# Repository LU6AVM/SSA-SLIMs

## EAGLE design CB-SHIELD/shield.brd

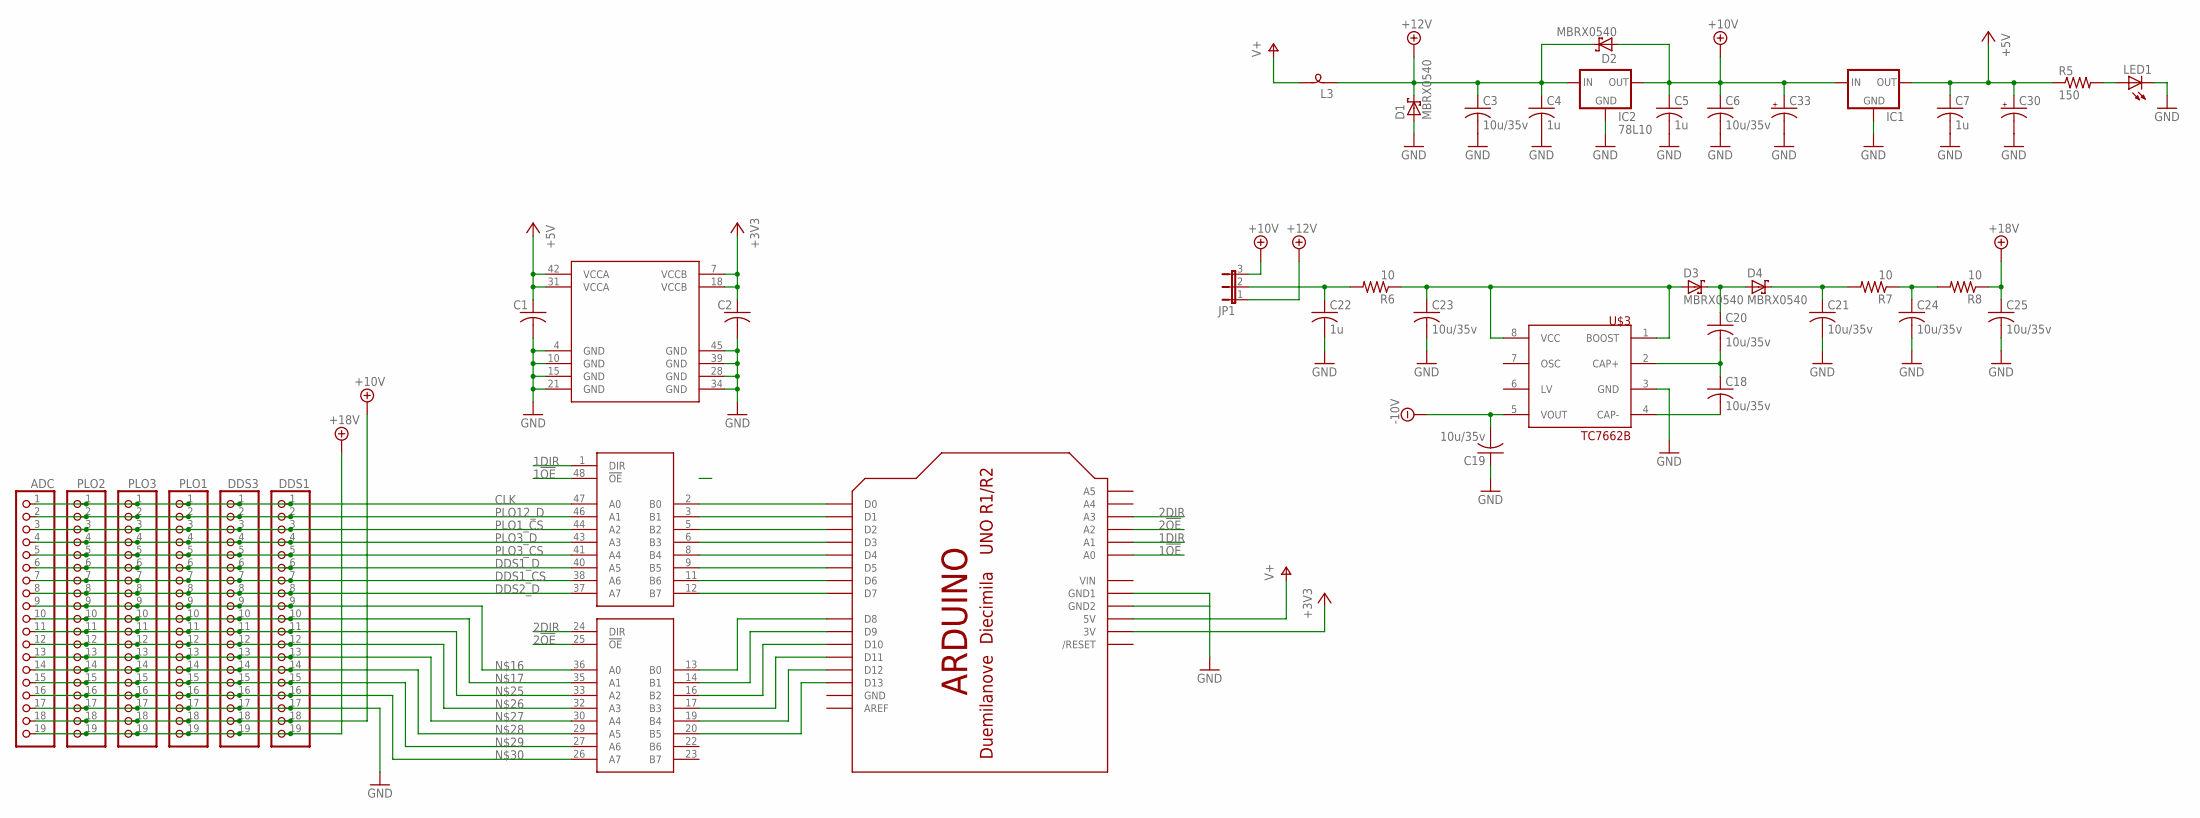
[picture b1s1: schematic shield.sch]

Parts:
ADC: PINHD-1X19; 1X19
C1, C2: C-USC0805; C0805
C3, C6, C18, C19, C20, C21, C23, C24, C25: 10u/35v; C1206
C4, C5, C7, C22: 1u; C0603
C30, C33: CPOL-USE2.5-6; E2,5-6
D1, D2, D3, D4: MBRX0540; SOD323-R
DDS1, DDS3: PINHD-1X19; 1X19
IC1: 78MXXLSOT-89; SOT89-BCE
IC2: 78L10; 78XXS
JP1: JP2E; JP2
L3: SM-B5
LED1: LED5MM
PLO1, PLO2, PLO3: PINHD-1X19; 1X19
R5: 150; R0603
R6, R7, R8: 10; R0603
U$1: ARDUINO-NOHOLE
U$2: 74ALVC164245DL; SSO48
U$3: TC7662B; SO-08

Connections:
1!OE: U$1.A0, U$2.48 (!OE)
1DIR: U$1.A1, U$2.1 (DIR)
2!OE: U$1.A2, U$2.25 (!OE)
2DIR: U$1.A3, U$2.24 (DIR)
+3V3: C2.1, U$1.3V, U$2.7 (VCCB), U$2.18 (VCCB)
+5V: C1.1, C7.1, C30.+, IC1.B (OUT), R5.1, U$2.31 (VCCA), U$2.42 (VCCA)
+10V: ADC.18, C5.1, C6.1, C33.+, D2.A, DDS1.18, DDS3.18, IC1.E (IN), IC2.OUT, JP1.3, PLO1.18, PLO2.18, PLO3.18
+12V: C3.1, C4.1, D1.C, D2.C, IC2.IN, JP1.1, L3.1
+18V: ADC.19, C25.1, DDS1.19, DDS3.19, PLO1.19, PLO2.19, PLO3.19, R8.1
-10V: C19.2, U$3.5 (VOUT)
CLK: ADC.1, DDS1.1, DDS3.1, PLO1.1, PLO2.1, PLO3.1, U$2.47 (A0)
DDS1_CS: ADC.7, DDS1.7, DDS3.7, PLO1.7, PLO2.7, PLO3.7, U$2.38 (A6)
DDS1_D: ADC.6, DDS1.6, DDS3.6, PLO1.6, PLO2.6, PLO3.6, U$2.40 (A5)
DDS2_D: ADC.8, DDS1.8, DDS3.8, PLO1.8, PLO2.8, PLO3.8, U$2.37 (A7)
GND: ADC.17, C1.2, C2.2, C3.2, C4.2, C5.2, C6.2, C7.2, C19.1, C21.2, C22.2, C23.2, C24.2, C25.2, C30.-, C33.-, D1.A, DDS1.17, DDS3.17, IC1.C (GND), IC2.GND, LED1.K (C), PLO1.17, PLO2.17, PLO3.17, U$1.GND, U$1.GND1, U$1.GND2, U$2.4 (GND), U$2.10 (GND), U$2.15 (GND), U$2.21 (GND), U$2.28 (GND), U$2.34 (GND), U$2.39 (GND), U$2.45 (GND), U$3.3 (GND)
unnamed: U$1.D8, U$2.13 (B0)
unnamed: U$1.D9, U$2.14 (B1)
unnamed: U$1.D10, U$2.16 (B2)
unnamed: U$1.D11, U$2.17 (B3)
unnamed: U$1.D12, U$2.19 (B4)
unnamed: U$1.D13, U$2.20 (B5)
unnamed: U$1.D7, U$2.12 (B7)
unnamed: U$1.D6, U$2.11 (B6)
unnamed: U$1.D5, U$2.9 (B5)
unnamed: U$1.D4, U$2.8 (B4)
unnamed: U$1.D3, U$2.6 (B3)
unnamed: U$1.D2, U$2.5 (B2)
unnamed: U$1.D1, U$2.3 (B1)
unnamed: U$1.D0, U$2.2 (B0)
unnamed: ADC.9, DDS1.9, DDS3.9, PLO1.9, PLO2.9, PLO3.9, U$2.36 (A0)
unnamed: ADC.10, DDS1.10, DDS3.10, PLO1.10, PLO2.10, PLO3.10, U$2.35 (A1)
unnamed: C22.1, JP1.2, R6.2
unnamed: C23.1, D3.A, R6.1, U$3.1 (BOOST), U$3.8 (VCC)
unnamed: C18.2, U$3.4 (CAP-)
unnamed: C18.1, C20.2, U$3.2 (CAP+)
unnamed: C20.1, D3.C, D4.A
unnamed: C21.1, D4.C, R7.2
unnamed: C24.1, R7.1, R8.2
unnamed: ADC.11, DDS1.11, DDS3.11, PLO1.11, PLO2.11, PLO3.11, U$2.33 (A2)
unnamed: ADC.12, DDS1.12, DDS3.12, PLO1.12, PLO2.12, PLO3.12, U$2.32 (A3)
unnamed: ADC.13, DDS1.13, DDS3.13, PLO1.13, PLO2.13, PLO3.13, U$2.30 (A4)
unnamed: ADC.14, DDS1.14, DDS3.14, PLO1.14, PLO2.14, PLO3.14, U$2.29 (A5)
unnamed: ADC.15, DDS1.15, DDS3.15, PLO1.15, PLO2.15, PLO3.15, U$2.27 (A6)
unnamed: ADC.16, DDS1.16, DDS3.16, PLO1.16, PLO2.16, PLO3.16, U$2.26 (A7)
unnamed: LED1.A, R5.2
PLO1_CS: ADC.3, DDS1.3, DDS3.3, PLO1.3, PLO2.3, PLO3.3, U$2.44 (A2)
PLO3_CS: ADC.5, DDS1.5, DDS3.5, PLO1.5, PLO2.5, PLO3.5, U$2.41 (A4)
PLO3_D: ADC.4, DDS1.4, DDS3.4, PLO1.4, PLO2.4, PLO3.4, U$2.43 (A3)
PLO12_D: ADC.2, DDS1.2, DDS3.2, PLO1.2, PLO2.2, PLO3.2, U$2.46 (A1)
V+: L3.2, U$1.5V
VIN: U$1.VIN

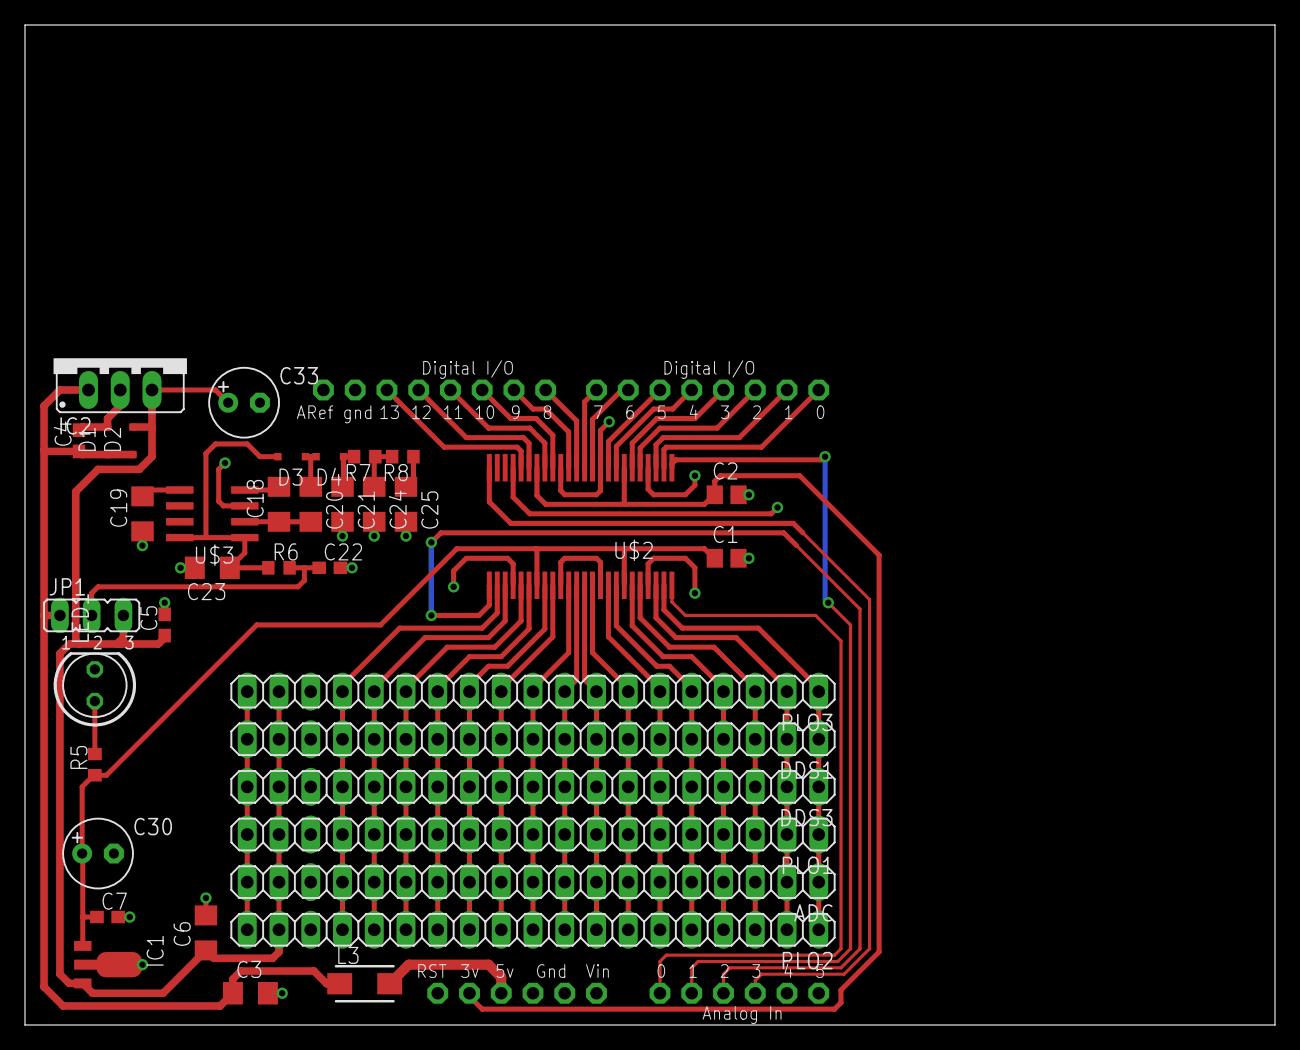
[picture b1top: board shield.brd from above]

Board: 2 copper layers, 100.0 x 80.0 mm, 39 parts (0 on the bottom side), 50 nets.

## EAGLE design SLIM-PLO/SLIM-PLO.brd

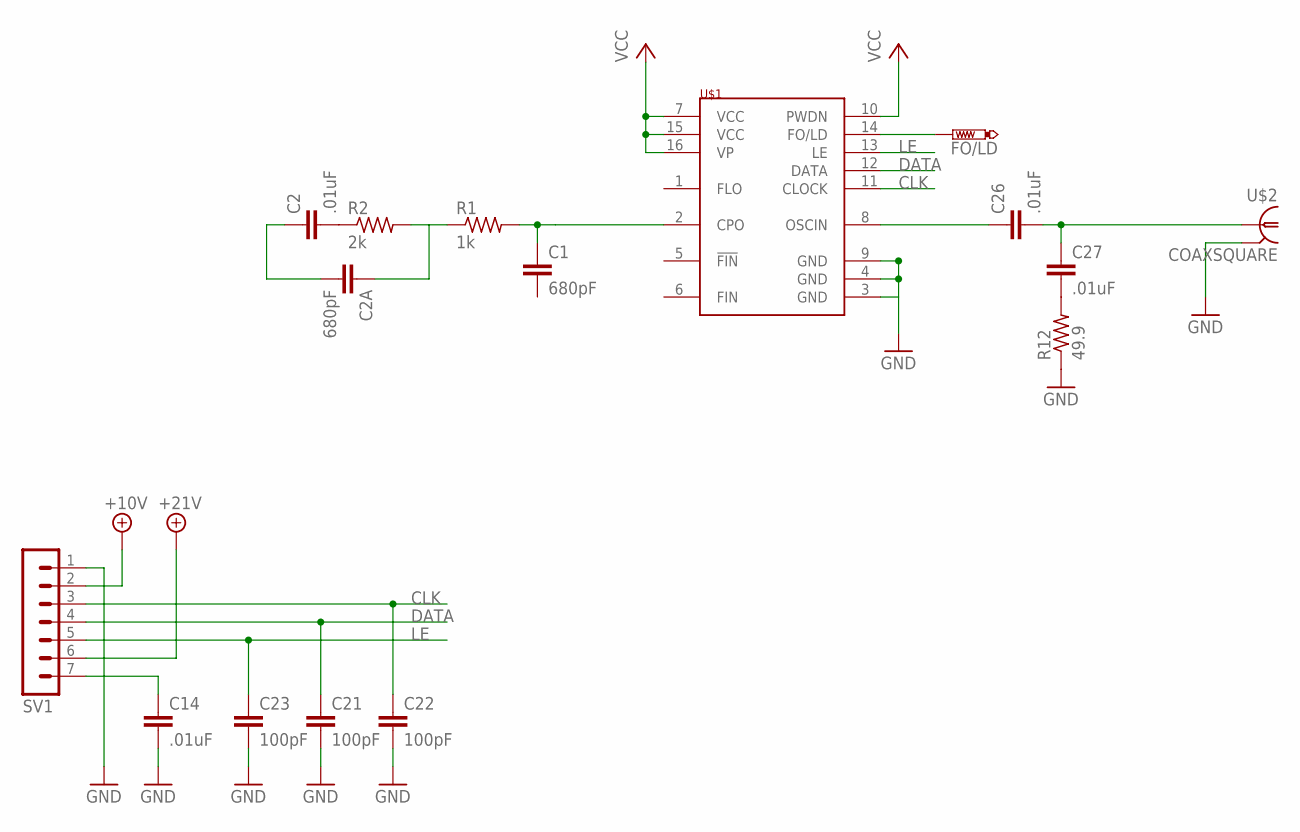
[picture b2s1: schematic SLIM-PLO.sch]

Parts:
C1, C2A: 680pF; C0805
C2, C14, C26, C27: .01uF; C0805
C21, C22, C23: 100pF; C0805
FO/LD: PTR1B1,27; B1,27
R1: 1k; M0805
R2: 2k; M0805
R12: 49.9; M0805
SV1: MA07-1
U$1: LMX2326; TSSOP16
U$2: COAXSQUARE; SLIM_COAX_PAD

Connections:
+10V: SV1.2
+21V: SV1.6
CLK: C22.1, SV1.3, U$1.11 (CLOCK)
DATA: C21.1, SV1.4, U$1.12 (DATA)
GND: C14.2, C21.2, C22.2, C23.2, R12.1, SV1.1, U$1.3 (GND), U$1.4 (GND), U$1.9 (GND), U$2.P$2 (GND)
LE: C23.1, SV1.5, U$1.13 (LE)
unnamed: FO/LD.TP, U$1.14 (FO/LD)
unnamed: C14.1, SV1.7
unnamed: C26.1, U$1.8 (OSCIN)
unnamed: C26.2, C27.1, U$2.P$1 (1)
unnamed: C27.2, R12.2
unnamed: C1.1, R1.2, U$1.2 (CPO)
unnamed: C2.2, R2.1
unnamed: C2A.1, R1.1, R2.2
unnamed: C2.1, C2A.2
VCC: U$1.7 (VCC), U$1.10 (PWDN), U$1.15 (VCC), U$1.16 (VP)

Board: 2 copper layers, 16 parts (0 on the bottom side), 14 nets, no tracks yet.
